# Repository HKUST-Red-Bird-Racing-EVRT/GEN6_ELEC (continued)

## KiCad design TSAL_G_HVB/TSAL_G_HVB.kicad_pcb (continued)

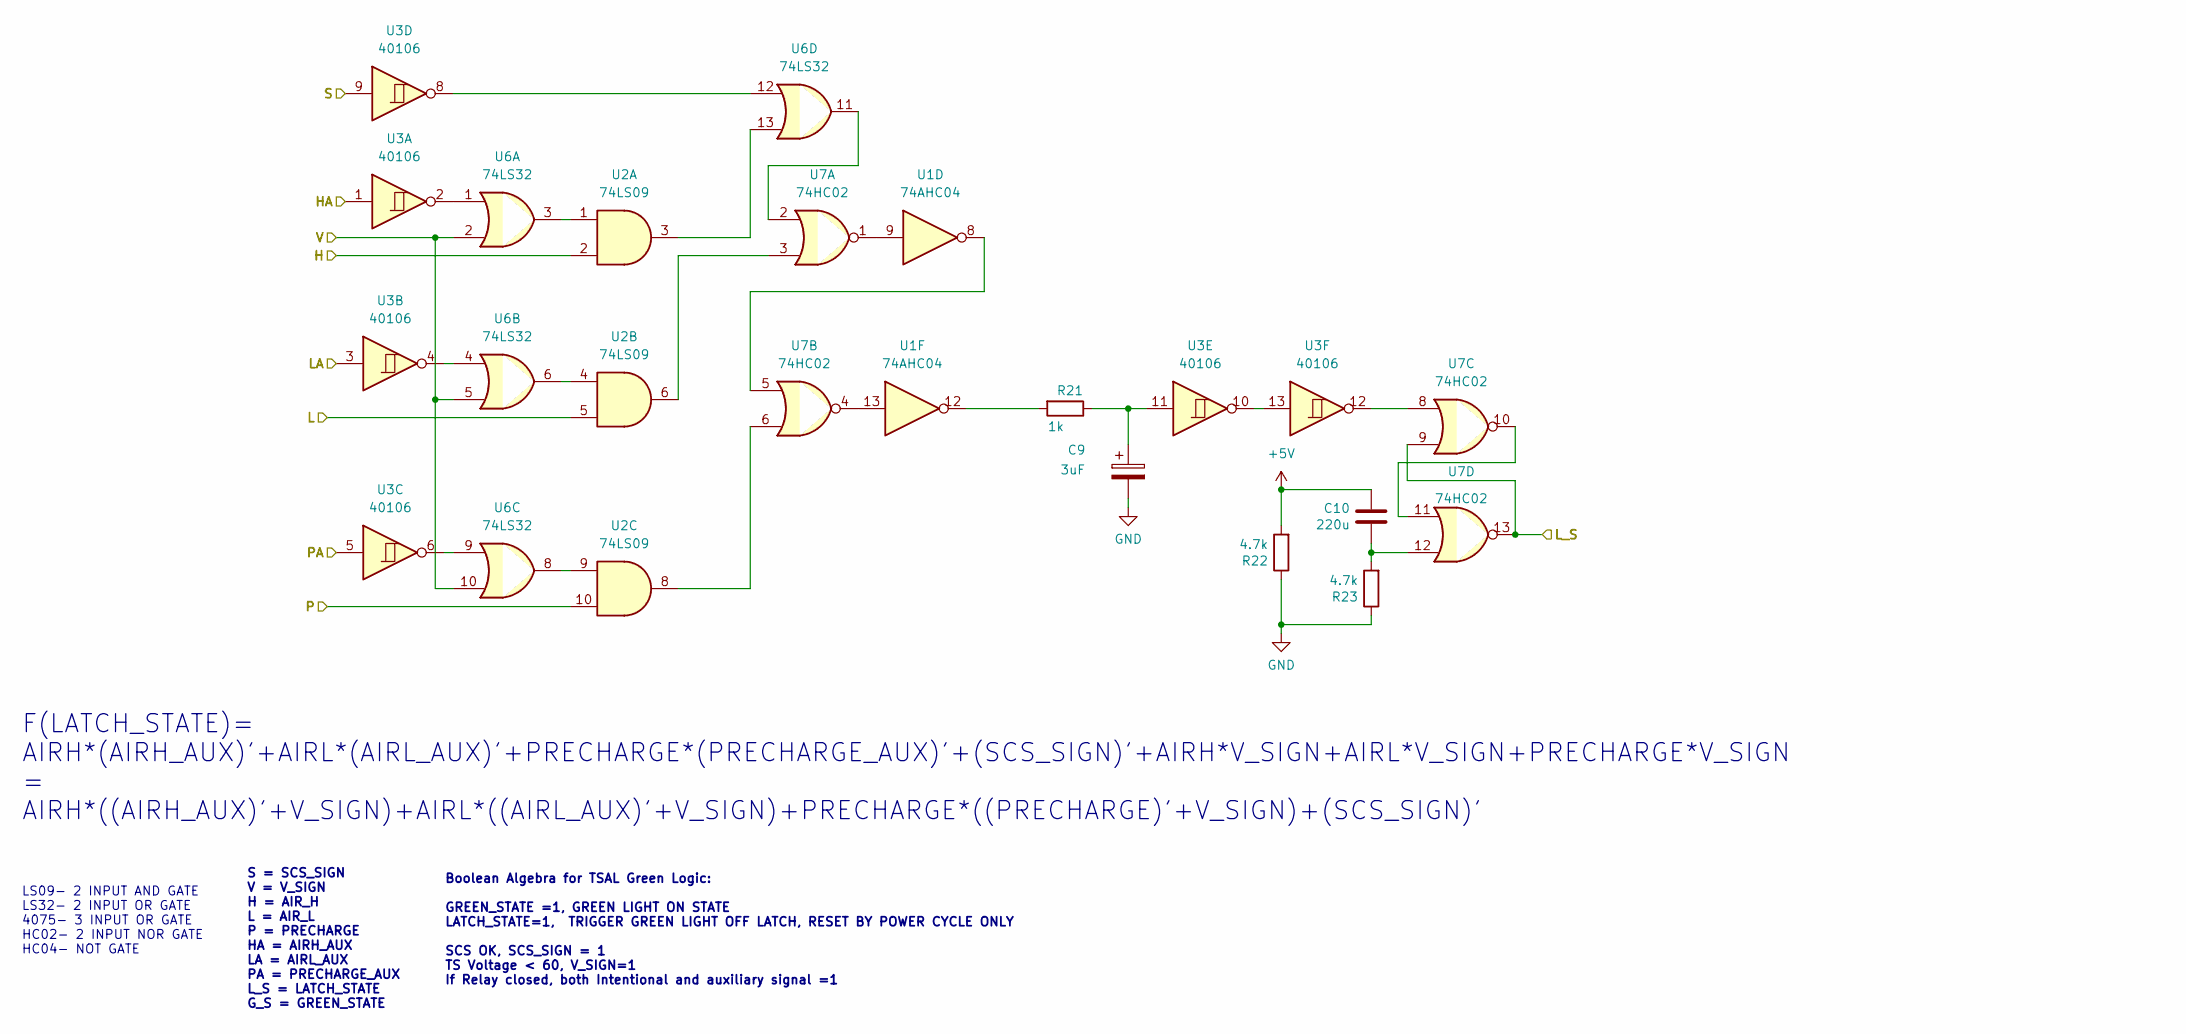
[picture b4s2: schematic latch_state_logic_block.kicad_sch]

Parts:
C9: 3uF; CP_Radial_D5.0mm_P2.50mm
C10: 220u; CP_Radial_D5.0mm_P2.50mm
R21: 1k; R_0805_2012Metric_Pad1.20x1.40mm_HandSolder_L
R22, R23: 4.7k; R_0805_2012Metric_Pad1.20x1.40mm_HandSolder_L
U1: 74AHC04; SOIC127P600X175-14N
U2: 74LS09; SOIC127P600X175-14N
U3: 40106; SOIC127P600X175-14N
U6: 74LS32; SOIC127P600X175-14N
U7: 74HC02; SOIC127P600X175-14N

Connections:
+5V: C10.1, R22.2; also elsewhere on the board
AIRH: U2.2; also elsewhere on the board
AIRH_AUX: U3.1; also elsewhere on the board
AIRL: U2.5; also elsewhere on the board
AIRL_AUX: U3.3; also elsewhere on the board
GND: C9.2, R22.1, R23.1; also elsewhere on the board
LATCH_STATE: U7.9, U7.13; also elsewhere on the board
unnamed: C9.1, R21.1, U3.11
unnamed: C10.2, R23.2, U7.12
unnamed: R21.2, U1.12
unnamed: U1.8, U7.5
unnamed: U1.9, U7.1
unnamed: U1.13, U7.4
unnamed: U2.1, U6.3
unnamed: U2.3, U6.13
unnamed: U2.4, U6.6
unnamed: U2.6, U7.3
unnamed: U2.8, U7.6
unnamed: U2.9, U6.8
unnamed: U3.2, U6.1
unnamed: U3.4, U6.4
unnamed: U3.6, U6.9
unnamed: U3.8, U6.12
unnamed: U3.10, U3.13
unnamed: U3.12, U7.8
unnamed: U6.11, U7.2
unnamed: U7.10, U7.11
PRECHARGE: U2.10; also elsewhere on the board
PRECHARGE_AUX: U3.5; also elsewhere on the board
SCS_SIGN_IN: U3.9; also elsewhere on the board
V_SIGN: U6.2, U6.5, U6.10; also elsewhere on the board

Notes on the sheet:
F(LATCH_STATE)= AIRH*(AIRH_AUX)'+AIRL*(AIRL_AUX)'+PRECHARGE*(PRECHARGE_AUX)'+(SCS_SIGN)'+AIRH*V_SIGN+AIRL*V_SIGN+PRECHARGE*V_SIGN = AIRH*((AIRH_AUX)'+V_SIGN)+AIRL*((AIRL_AUX)'+V_SIGN)+PRECHARGE*((PRECHARGE)'+V_SIGN)+(SCS_SIGN)'
LS09- 2 INPUT AND GATE LS32- 2 INPUT OR GATE 4075- 3 INPUT OR GATE HC02- 2 INPUT NOR GATE HC04- NOT GATE
S = SCS_SIGN V = V_SIGN H = AIR_H L = AIR_L P = PRECHARGE HA = AIRH_AUX LA = AIRL_AUX PA = PRECHARGE_AUX L_S = LATCH_STATE G_S = GREEN_STATE
Boolean Algebra for TSAL Green Logic: GREEN_STATE =1, GREEN LIGHT ON STATE LATCH_STATE=1, TRIGGER GREEN LIGHT OFF LATCH, RESET BY POWER CYCLE ONLY SCS OK, SCS_SIGN = 1 TS Voltage < 60, V_SIGN=1 If Relay closed, both Intentional and auxiliary signal =1

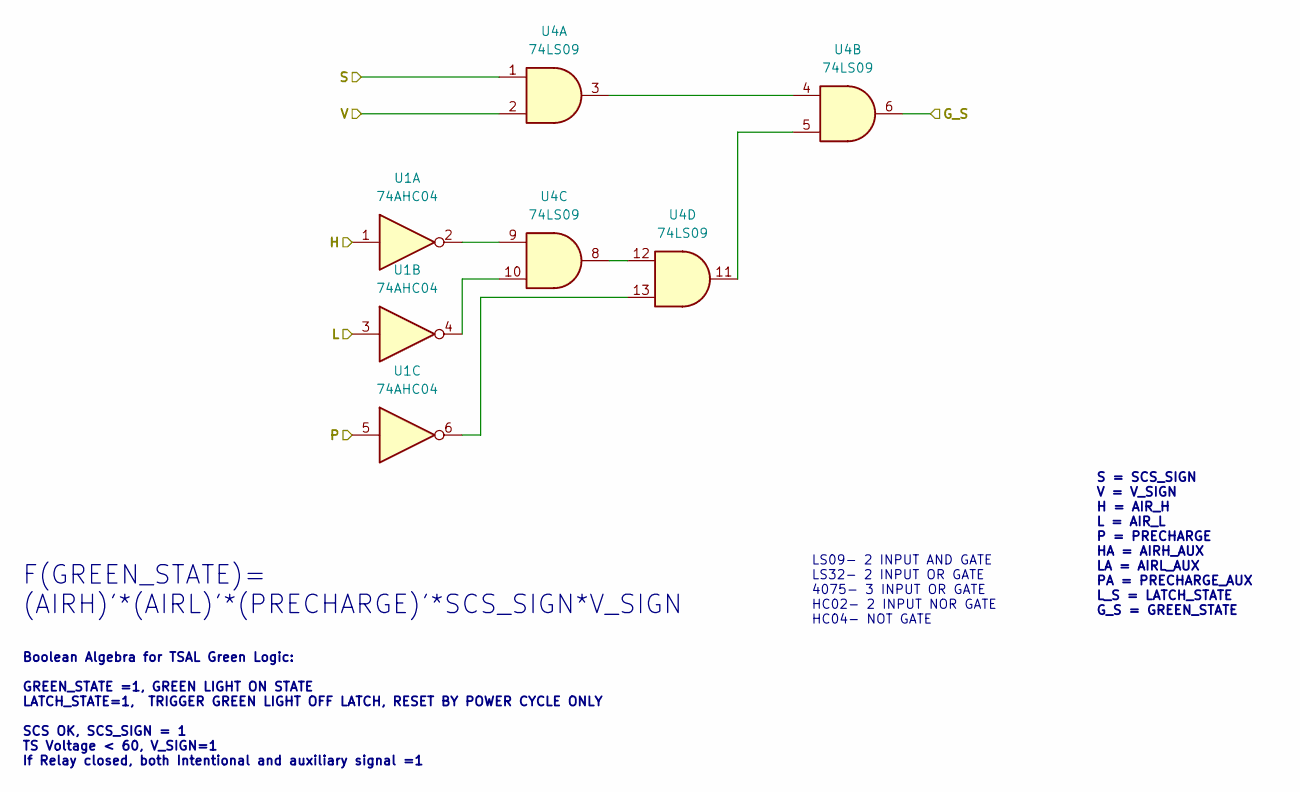
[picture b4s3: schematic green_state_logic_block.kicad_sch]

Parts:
U1: 74AHC04; SOIC127P600X175-14N
U4: 74LS09; SOIC127P600X175-14N

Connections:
AIRH: U1.1; also elsewhere on the board
AIRL: U1.3; also elsewhere on the board
GREEN_STATE: U4.6; also elsewhere on the board
unnamed: U1.2, U4.9
unnamed: U1.4, U4.10
unnamed: U1.6, U4.13
unnamed: U4.3, U4.4
unnamed: U4.5, U4.11
unnamed: U4.8, U4.12
PRECHARGE: U1.5; also elsewhere on the board
SCS_SIGN_IN: U4.1; also elsewhere on the board
V_SIGN: U4.2; also elsewhere on the board

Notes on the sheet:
S = SCS_SIGN V = V_SIGN H = AIR_H L = AIR_L P = PRECHARGE HA = AIRH_AUX LA = AIRL_AUX PA = PRECHARGE_AUX L_S = LATCH_STATE G_S = GREEN_STATE
LS09- 2 INPUT AND GATE LS32- 2 INPUT OR GATE 4075- 3 INPUT OR GATE HC02- 2 INPUT NOR GATE HC04- NOT GATE
Boolean Algebra for TSAL Green Logic: GREEN_STATE =1, GREEN LIGHT ON STATE LATCH_STATE=1, TRIGGER GREEN LIGHT OFF LATCH, RESET BY POWER CYCLE ONLY SCS OK, SCS_SIGN = 1 TS Voltage < 60, V_SIGN=1 If Relay closed, both Intentional and auxiliary signal =1
F(GREEN_STATE)= (AIRH)'*(AIRL)'*(PRECHARGE)'*SCS_SIGN*V_SIGN

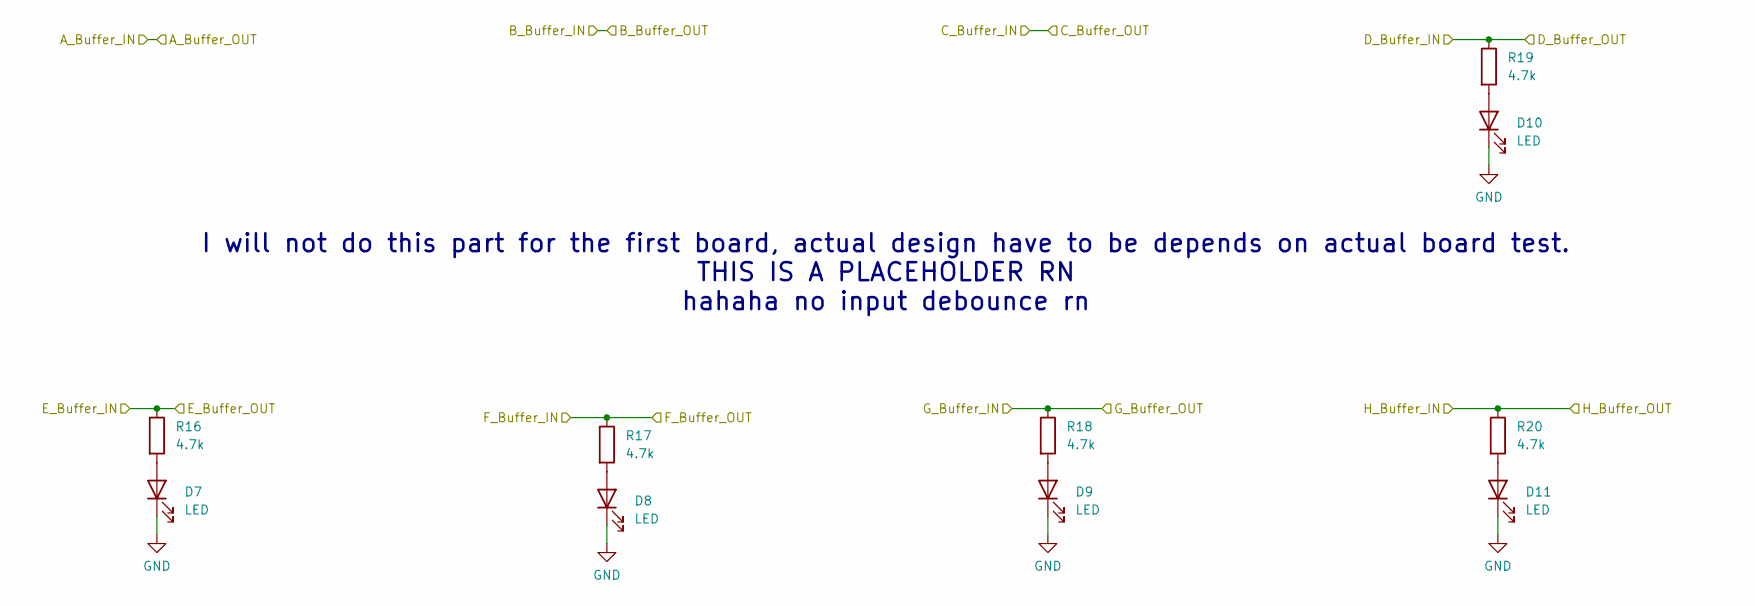
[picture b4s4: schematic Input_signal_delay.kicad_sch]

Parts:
D7, D8, D9, D10, D11: LED; LED_0805_2012Metric_Pad1.45x1.40mm_HandSolder
R16, R17, R18, R19, R20: 4.7k; R_0805_2012Metric_Pad1.20x1.40mm_HandSolder_L

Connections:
AIRH_AUX: R19.1; also elsewhere on the board
AIRL_AUX: R16.1; also elsewhere on the board
GND: D7.1 (K), D8.1 (K), D9.1 (K), D10.1 (K), D11.1 (K); also elsewhere on the board
unnamed: D7.2 (A), R16.2
unnamed: D8.2 (A), R17.2
unnamed: D9.2 (A), R18.2
unnamed: D10.2 (A), R19.2
unnamed: D11.2 (A), R20.2
PRECHARGE_AUX: R17.1; also elsewhere on the board
SCS_SIGN_IN: R20.1; also elsewhere on the board
V_SIGN: R18.1; also elsewhere on the board

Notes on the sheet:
I will not do this part for the first board, actual design have to be depends on actual board test. THIS IS A PLACEHOLDER RN hahaha no input debounce rn

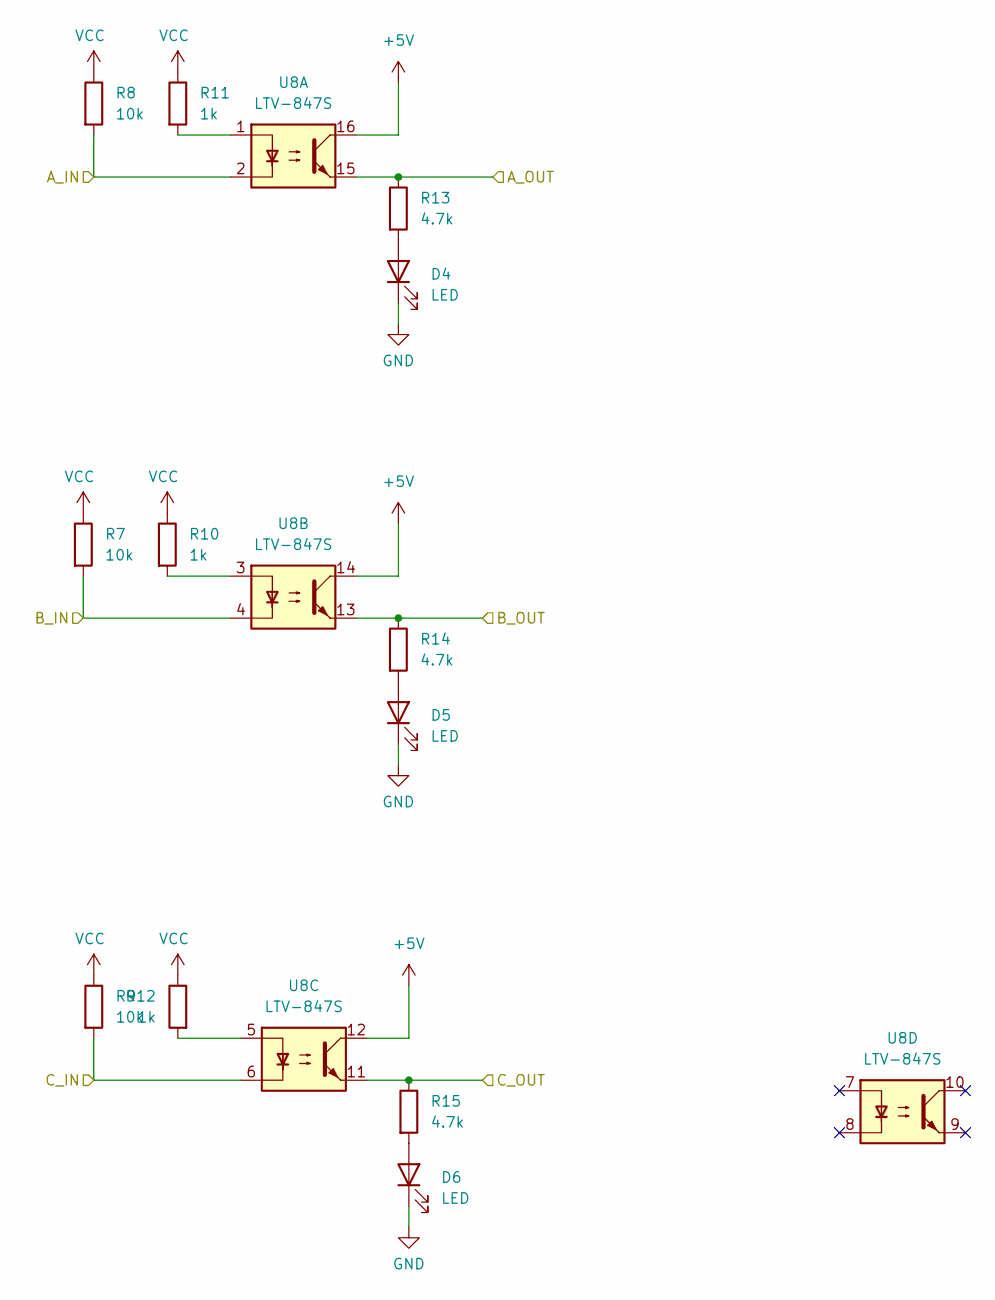
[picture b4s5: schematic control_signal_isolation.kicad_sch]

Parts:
D4, D5, D6: LED; LED_0805_2012Metric_Pad1.45x1.40mm_HandSolder
R7, R8, R9: 10k; R_0805_2012Metric_Pad1.20x1.40mm_HandSolder_L
R10, R11, R12: 1k; R_0805_2012Metric_Pad1.20x1.40mm_HandSolder_L
R13, R14, R15: 4.7k; R_0805_2012Metric_Pad1.20x1.40mm_HandSolder_L
U8: LTV-847S; SMDIP-16_W9.53mm

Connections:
+5V: U8.12, U8.14, U8.16; also elsewhere on the board
AIRH: R13.1, U8.15; also elsewhere on the board
AIRH_IN: R8.2, U8.2; also elsewhere on the board
AIRL: R14.1, U8.13; also elsewhere on the board
AIRL_IN: R7.2, U8.4; also elsewhere on the board
GND: D4.1 (K), D5.1 (K), D6.1 (K); also elsewhere on the board
unnamed: D4.2 (A), R13.2
unnamed: D5.2 (A), R14.2
unnamed: D6.2 (A), R15.2
unnamed: R10.2, U8.3
unnamed: R11.2, U8.1
unnamed: R12.2, U8.5
PRECHARGE: R15.1, U8.11; also elsewhere on the board
PRECHARGE_IN: R9.2, U8.6; also elsewhere on the board
VCC: R7.1, R8.1, R9.1, R10.1, R11.1, R12.1; also elsewhere on the board

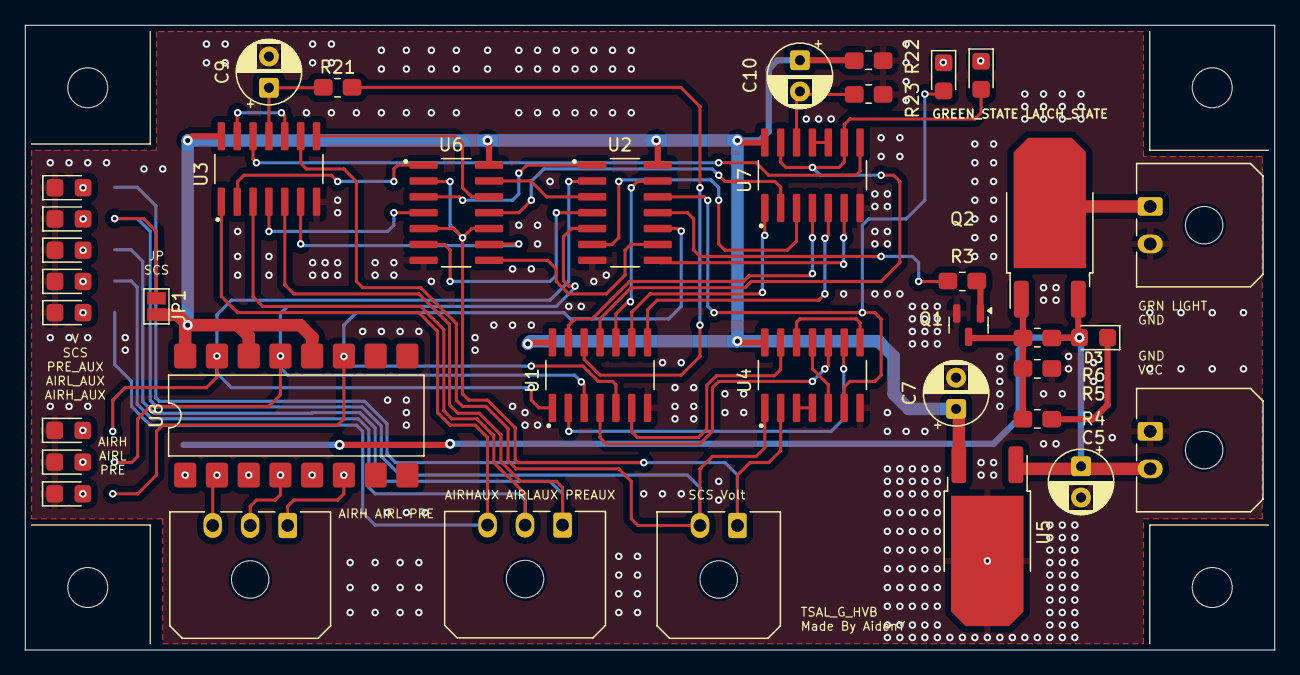
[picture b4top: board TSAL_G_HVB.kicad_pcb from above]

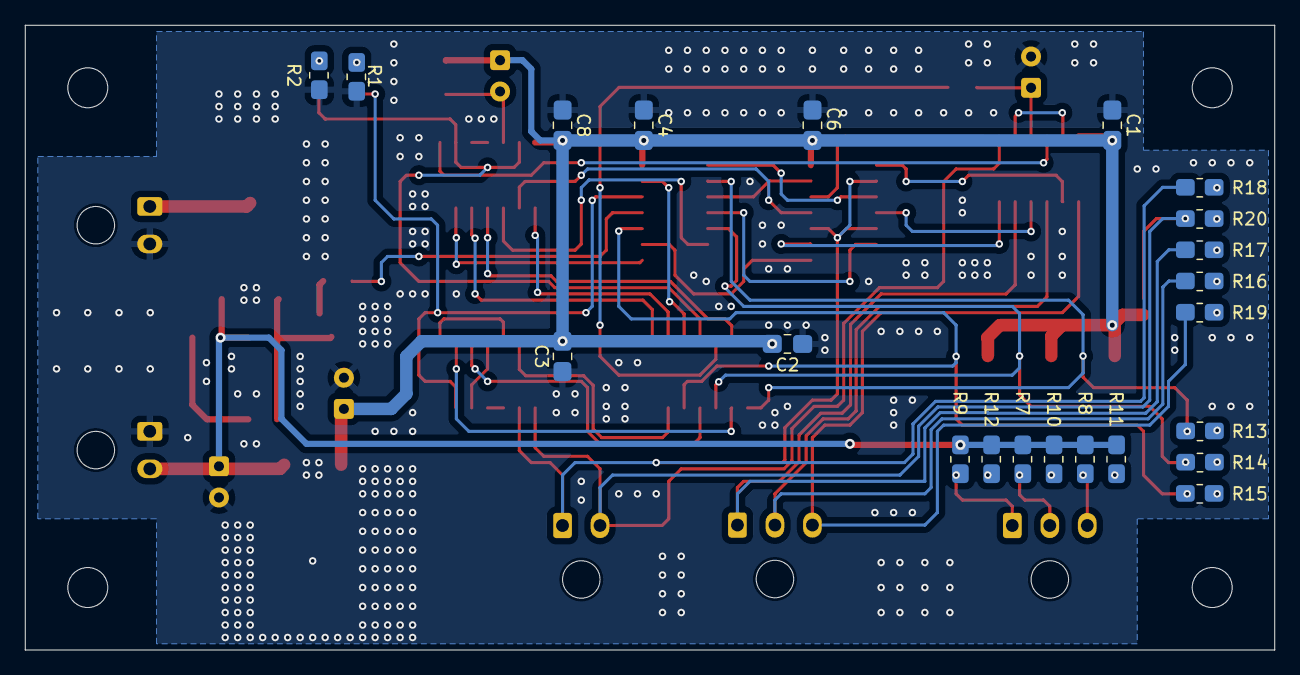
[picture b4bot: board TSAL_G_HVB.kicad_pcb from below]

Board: 2 copper layers, 100.0 x 50.0 mm, 64 parts (22 on the bottom side), 61 nets.

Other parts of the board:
H1, H2, H3, H4: MountingHole; MountingHole_3.2mm_M3

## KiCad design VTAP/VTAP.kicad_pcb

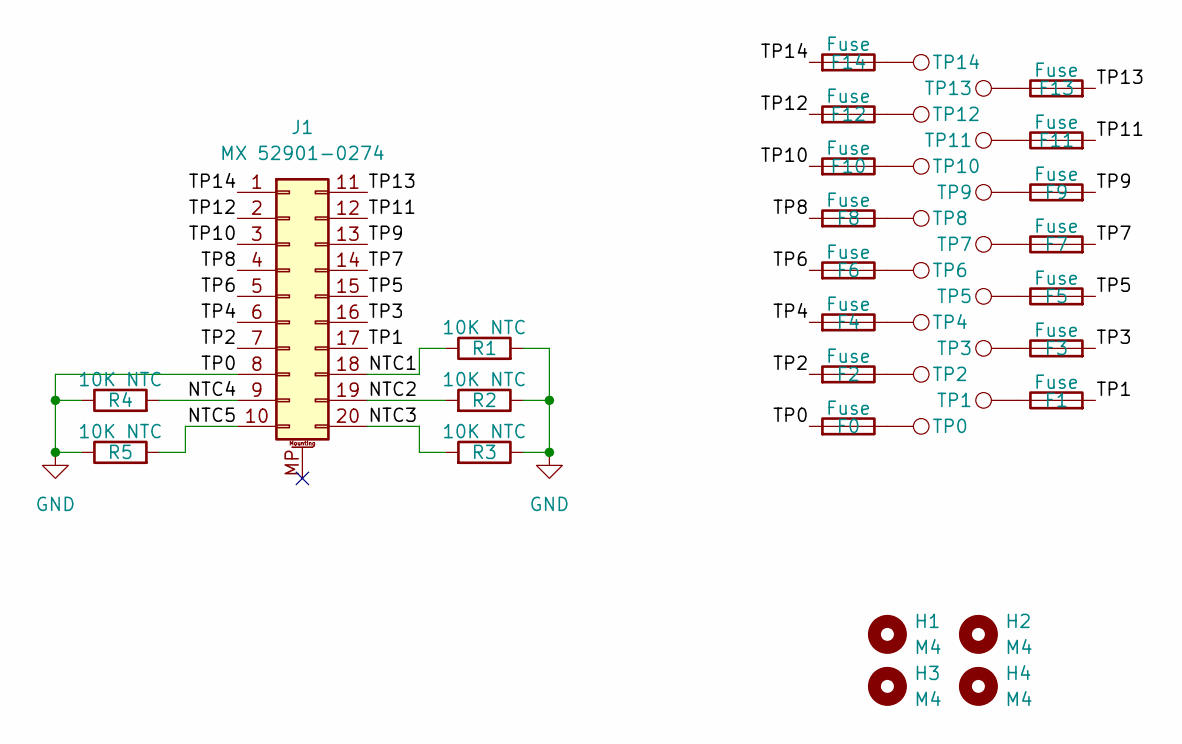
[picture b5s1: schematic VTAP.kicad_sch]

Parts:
F0, F1, F2, F3, F4, F5, F6, F7, F8, F9, F10, F11, F12, F13, F14: Fuse; R_1206_3216Metric_Pad1.30x1.75mm_HandSolder_RMC
H1, H2, H3, H4: M4; MountingHole_4.3mm_M4
J1: MX 52901-0274; CON_529010274_MOL
R1, R2, R3, R4, R5: 10K NTC; R_0805_2012Metric_Pad1.20x1.40mm_HandSolder_L
TP0, TP1, TP2, TP3, TP4, TP5, TP6, TP7, TP8, TP9, TP10, TP11, TP12, TP13, TP14: TestPoint; Untitled

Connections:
/NTC1: J1.18, R1.1
/NTC2: J1.19, R2.2
/NTC3: J1.20, R3.2
/NTC4: J1.9, R4.2
/NTC5: J1.10, R5.2
/TP1: F1.2, J1.17
/TP2: F2.2, J1.7
/TP3: F3.2, J1.16
/TP4: F4.2, J1.6
/TP5: F5.2, J1.15
/TP6: F6.2, J1.5
/TP7: F7.2, J1.14
/TP8: F8.2, J1.4
/TP9: F9.2, J1.13
/TP10: F10.2, J1.3
/TP11: F11.2, J1.12
/TP12: F12.2, J1.2
/TP13: F13.2, J1.11
/TP14: F14.2, J1.1
GND: F0.2, J1.8, R1.2, R2.1, R3.1, R4.1, R5.1
unnamed: F0.1, TP0.1
unnamed: F1.1, TP1.1
unnamed: F2.1, TP2.1
unnamed: F3.1, TP3.1
unnamed: F4.1, TP4.1
unnamed: F5.1, TP5.1
unnamed: F6.1, TP6.1
unnamed: F7.1, TP7.1
unnamed: F8.1, TP8.1
unnamed: F9.1, TP9.1
unnamed: F10.1, TP10.1
unnamed: F11.1, TP11.1
unnamed: F12.1, TP12.1
unnamed: F13.1, TP13.1
unnamed: F14.1, TP14.1

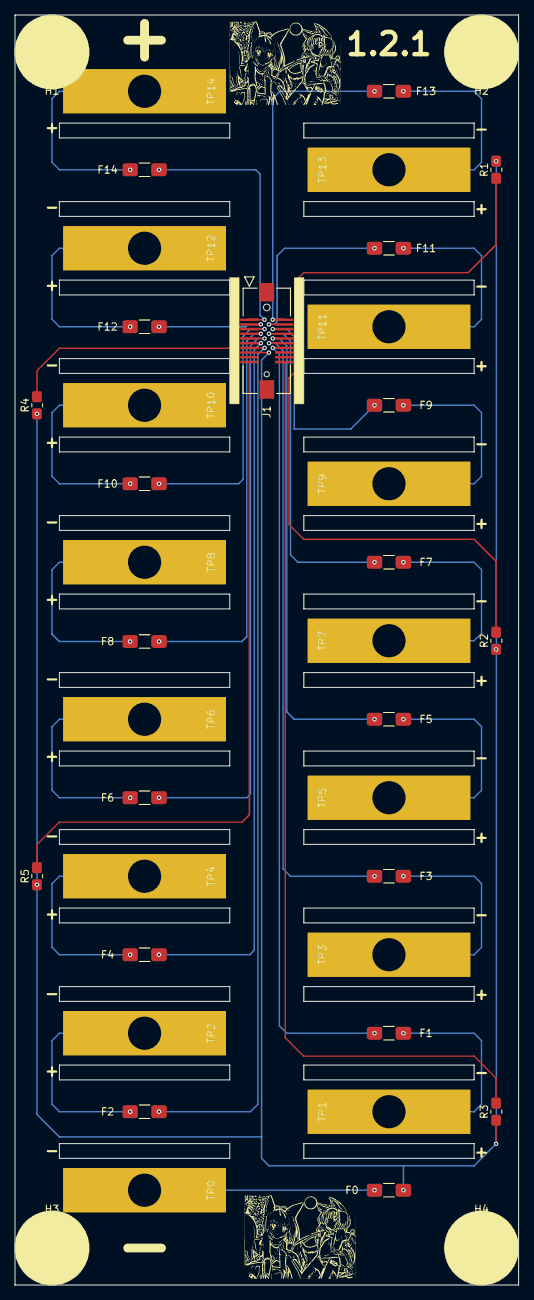
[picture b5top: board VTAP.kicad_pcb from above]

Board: 2 copper layers, 68.0 x 171.5 mm, 40 parts (0 on the bottom side), 35 nets.

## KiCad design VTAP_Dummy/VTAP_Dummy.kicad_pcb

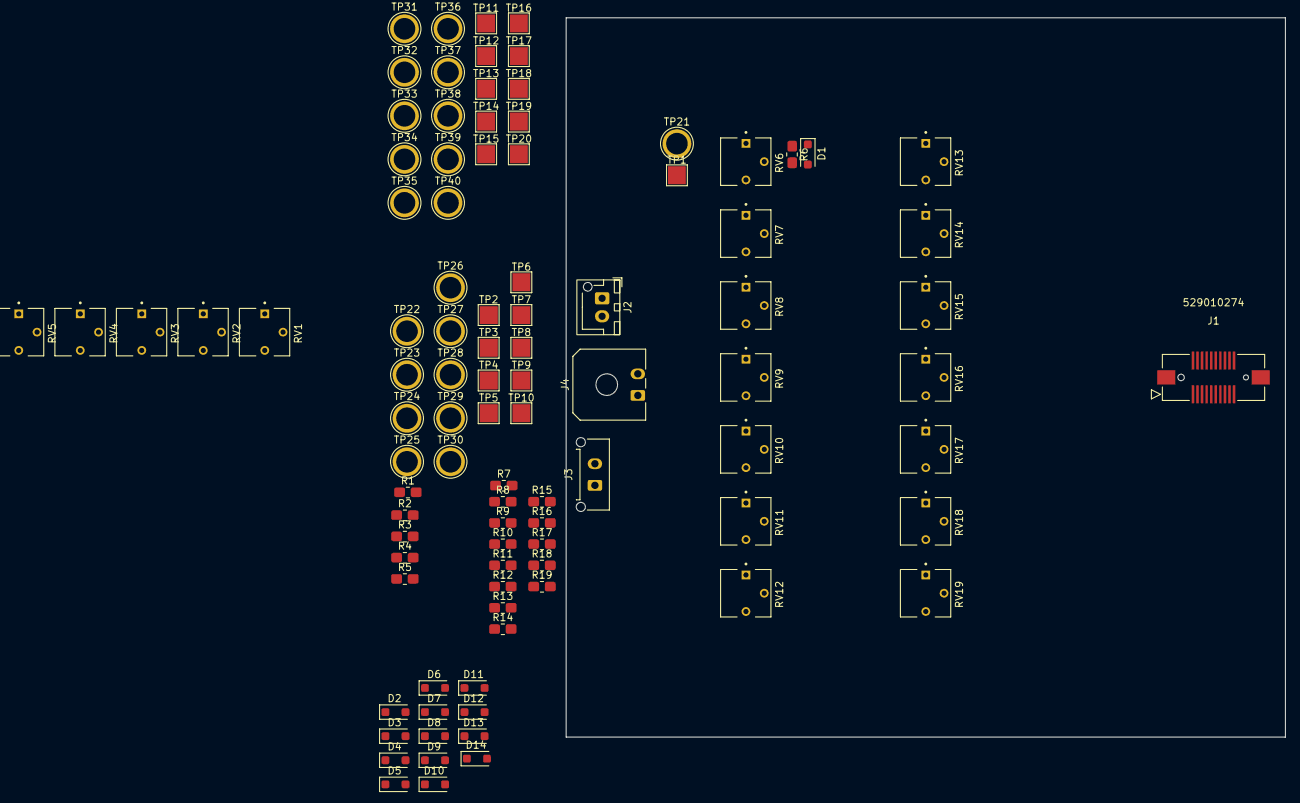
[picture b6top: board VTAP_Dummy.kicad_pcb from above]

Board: 2 copper layers, 100.0 x 100.0 mm, 96 parts (0 on the bottom side), 20 nets, no tracks yet.

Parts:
D1, D2, D3, D4, D5, D6, D7, D8, D9, D10, D11, D12, D13, D14: BZT52B5V1; D_SOD-123F
J1: MX 52901-0274; CON_529010274_MOL
J2: Conn_01x02_Socket; JST_XH_B2B-XH-AM_1x02_P2.50mm_Vertical
J3: Conn_01x02_Socket; Molex_Micro-Fit_3.0_43650-0215_1x02_P3.00mm_Vertical
J4: Conn_01x02_Socket; Molex_Micro-Fit_3.0_43650-0200_1x02_P3.00mm_Horizontal
R1, R2, R3, R4, R5: 10K NTC; R_0805_2012Metric_Pad1.20x1.40mm_HandSolder_L
R6, R7, R8, R9, R10, R11, R12, R13, R14, R15, R16, R17, R18, R19: 10k; R_0805_2012Metric_Pad1.20x1.40mm_HandSolder_L
RV1, RV2, RV3, RV4, RV5, RV6, RV7, RV8, RV9, RV10, RV11, RV12, RV13, RV14, RV15, RV16, RV17, RV18, RV19: 10k; TRIM_3362P-1-103
TP1, TP2, TP3, TP4, TP5, TP6, TP7, TP8, TP9, TP10, TP11, TP12, TP13, TP14, TP15, TP16, TP17, TP18, TP19, TP20: TestPoint; TestPoint_Pad_2.5x2.5mm
TP21, TP22, TP23, TP24, TP25, TP26, TP27, TP28, TP29, TP30, TP31, TP32, TP33, TP34, TP35, TP36, TP37, TP38, TP39, TP40: TestPoint; TestPoint_Plated_Hole_D3.0mm

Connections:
/NTC1: J1.18, R1.1, RV1.1, TP13.1 (1_1), TP33.1 (1_1)
/NTC2: J1.19, R2.2, RV2.1, TP12.1 (1_1), TP32.1 (1_1)
/NTC3: J1.20, R3.2, RV3.1, TP11.1 (1_1), TP31.1 (1_1)
/NTC4: J1.9, R4.1, RV4.1, TP9.1 (1_1), TP29.1 (1_1)
/NTC5: J1.10, R5.1, RV5.1, TP10.1 (1_1), TP30.1 (1_1)
/TP1: D13.2 (A), D14.1 (K), J1.17, R18.2, R19.1, RV18.2, RV18.3, RV19.1, TP14.1 (1_1), TP34.1 (1_1)
/TP2: D12.2 (A), D13.1 (K), J1.7, R17.2, R18.1, RV17.2, RV17.3, RV18.1, TP7.1 (1_1), TP27.1 (1_1)
/TP3: D11.2 (A), D12.1 (K), J1.16, R16.2, R17.1, RV16.2, RV16.3, RV17.1, TP15.1 (1_1), TP35.1 (1_1)
/TP4: D10.2 (A), D11.1 (K), J1.6, R15.2, R16.1, RV15.2, RV15.3, RV16.1, TP6.1 (1_1), TP26.1 (1_1)
/TP5: D9.2 (A), D10.1 (K), J1.15, R14.2, R15.1, RV14.2, RV14.3, RV15.1, TP16.1 (1_1), TP36.1 (1_1)
/TP6: D8.2 (A), D9.1 (K), J1.5, R13.2, R14.1, RV13.2, RV13.3, RV14.1, TP5.1 (1_1), TP25.1 (1_1)
/TP7: D7.2 (A), D8.1 (K), J1.14, R12.2, R13.1, RV12.2, RV12.3, RV13.1, TP17.1 (1_1), TP37.1 (1_1)
/TP8: D6.2 (A), D7.1 (K), J1.4, R11.2, R12.1, RV11.2, RV11.3, RV12.1, TP4.1 (1_1), TP24.1 (1_1)
/TP9: D5.2 (A), D6.1 (K), J1.13, R10.2, R11.1, RV10.2, RV10.3, RV11.1, TP18.1 (1_1), TP38.1 (1_1)
/TP10: D4.2 (A), D5.1 (K), J1.3, R9.2, R10.1, RV9.2, RV9.3, RV10.1, TP3.1 (1_1), TP23.1 (1_1)
/TP11: D3.2 (A), D4.1 (K), J1.12, R8.2, R9.1, RV8.2, RV8.3, RV9.1, TP19.1 (1_1), TP39.1 (1_1)
/TP12: D2.2 (A), D3.1 (K), J1.2, R7.2, R8.1, RV7.2, RV7.3, RV8.1, TP2.1 (1_1), TP22.1 (1_1)
/TP13: D1.2 (A), D2.1 (K), J1.11, R6.2, R7.1, RV6.2, RV6.3, RV7.1, TP20.1 (1_1), TP40.1 (1_1)
GND: D14.2 (A), J1.8, J2.2, J3.2, J4.2, R1.2, R2.1, R3.1, R4.2, R5.2, R19.2, RV1.2, RV1.3, RV2.2, RV2.3, RV3.2, RV3.3, RV4.2, RV4.3, RV5.2, RV5.3, RV19.2, RV19.3, TP8.1 (1_1), TP28.1 (1_1)
VCC: D1.1 (K), J1.1, J2.1, J3.1, J4.1, R6.1, RV6.1, TP1.1 (1_1), TP21.1 (1_1)

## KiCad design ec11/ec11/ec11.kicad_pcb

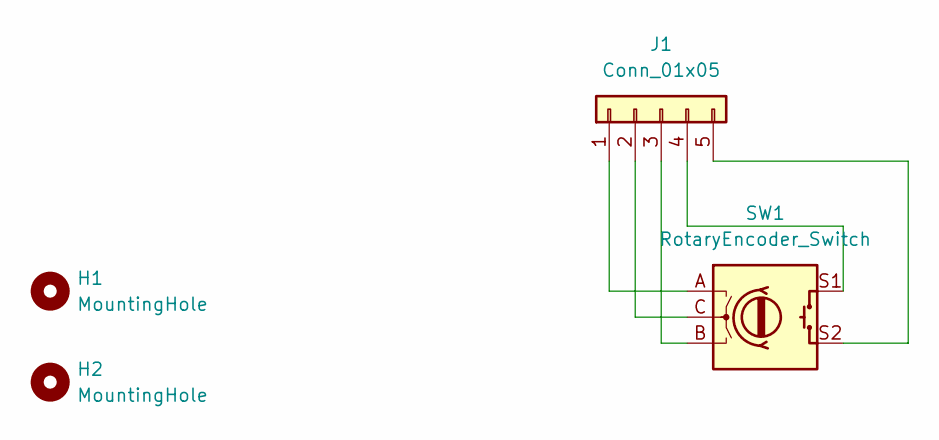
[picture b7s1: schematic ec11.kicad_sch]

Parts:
H1, H2: MountingHole; MountingHole_4.3mm_M4
J1: Conn_01x05; CONN_SD-43650-008_05_MOL
SW1: RotaryEncoder_Switch; RotaryEncoder_Alps_EC11E-Switch_Vertical_H20mm

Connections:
unnamed: J1.1, SW1.A
unnamed: J1.2, SW1.C
unnamed: J1.3, SW1.B
unnamed: J1.4, SW1.S1
unnamed: J1.5, SW1.S2

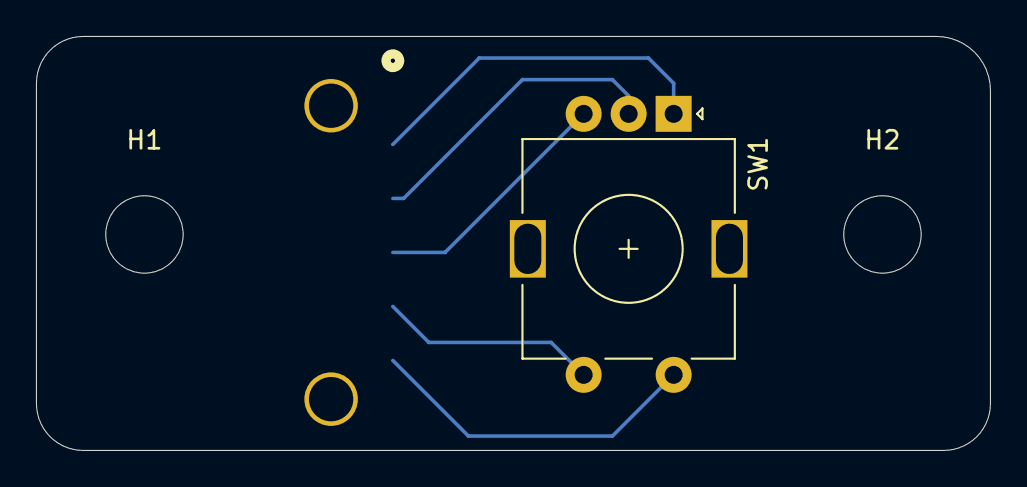
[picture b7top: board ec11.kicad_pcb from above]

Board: 2 copper layers, 53.0 x 23.0 mm, 4 parts (1 on the bottom side), 5 nets.
